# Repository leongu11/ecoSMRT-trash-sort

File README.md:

# ecoSMRT

## Overview
(this is my second README for this project -- I accidentally deleted the first one)
ecoSMRT is an edge AI project which determines if an article of trash is a recyclable (bottle) or not and sorts it accordingly.
It uses a refined version of MobileNetV2's CNN (convolutional neural networks) specifically for this task to make quality inferences. The model is around 60-70% accuracy when it comes to strong confidences over the 90% threshold.
I have logged nearly 45+ hours working on ecoSMRT as part of Hackclub's program, STASIS. Journal entries after every work session are also posted on the repository. 

## Incentive
Often times, managing waste can be overwhelming and done incorrectly. At the recycling level, nearly 76% of recyclables are lost at the household level (https://recyclingpartnership.org/residential-recycling-report/), and even those which are put into the recycling bin can be wrongly classified. As these wrongly-sorted articles of trash add up, the recycling process loses its efficiency, inflating unnecessary costs to over $3.5 billion yearly for the US (https://www.federalrecycling.com/industry-insights/common-recycling-mistakes-and-how-to-avoid-them/). As a direct result, recycling becomes more of a burden than a tool. Human error is exacerbating what recycling aims to fix: bettering the environment. Instead of looking towards refining the system, we should look to fix the root of the cause, our inaccuracies, by removing ourselves from the equation. AI is better than humans probably so like make a trash sorter ig 🤷‍♂️.

## Assembly Instructions
Use .stl files to print all 3d parts -- this includes the lid, the two edge mount pieces, the servo-lid adapter piece, and the camera mount (which is fixed to one of the edge mounts). NOTE: THE SERVO-LID ADAPTER PIECE REQUIRES A PAUSE IN THE PRINT TO SNAP ON THE HORN IN ORDER TO SEAL IT INSIDE THE PRINT! Slide the lid between the mounts to fix it in the center of the bin. Fasten the servo to the edge mount with two servo horn screws (which should have come with the servo) and connect the servo-lid adapter with the horn inside to the servo. Connect the adapter and the lid's extensions together-- glue is reccomended. The lid should now not rotate freely and rotating it should turn the servo, too. Attach a usb-c to usb-c onto the esp32 and camera and tape/glue to the top of the mount, allowing the camera to rest on the side of the mount. Connect the usb-c and flash the test-camera sketch onto the Xiao. It should return an IP to visit on the web to check the positioning of the camera. Adjust accordingly in order to have a clear view of the center of the bin. Using three jumper wires, solder the ends to both a capacitor and diode (optional, but recommended) using the schematic as a guide. Connect these jumpers to the servo, matching the power, ground, and signal accordingly. Once complete, flash the ecoSMRT-code onto the xiao. You should see inferences in the serial monitor and the lid rotating when those inferences pass the .95 -- or 95% -- threshold. Use the usb-c to power with any wall plug adapter or even laptop. 

## How ecoSMRT was made
I had originally settled for a more complex mechanical sorter, but the AI proved to be a challenge, so I simplified its design down to focus on firmware. The AI and curating a dataset which could yield decent results was also hard: At first, I was taking pre-existing datasets online, but the models were terrible. I did a lot of research and realized that I should probably use the native camera and setup for the training data, which turned out to work much better. Also, I switched from FOMO to MobileNet because like a month in I realized that image detection and classification were completely different (explanation found in journal). Everything else was relatively smooth sailing.

## Bill of Materials
| Component | Description | Cost | Link | 
|-----------|----------|-------------|-------|
| XIAO ESP32S3 Sense | Microcontroller with camera | $23.99 | [link](https://www.amazon.com/gp/product/B0CNL755KP/ref=ox_sc_act_title_2?smid=A2QTZX14X1D97I&th=1)
| MG90 servo | Sorting | $8.88 | [link](https://www.amazon.com/Seeed-Studio-XIAO-ESP32-Sense/dp/B0C69FFVHH?th=1)
## Hardware 
- MCU - Xiao ESP32S3-Sense w/ built-in camera module:
The Xiao ESP32 felt like the suitable choice because of its dual-core processors and built-in camera, which allowed the classification model to run smoothly locally, along with its GPIO capabilities.
Camera - OV2640 
- MG90 Microservo:
I have had my fair share of bad experience with the SG90 on multiple accounts, so I opted for its counterpart with metal-geared teeth, which seemed to be a good idea for tourque.

## Electronic Framework
I designed a schematic and PCB for this project in KiCAD

Schematic for wiring on perfboard:

PCB: 

I plan to use a perfboard using these as references for the physical project. 

## CAD / 3d Printed Parts

Parts are printed in PLA, amounting to around 300 grams of filament (although all my prototypes summed up to a kg spool)
These consist of the bin's lid, which revolves on small axis extensions. These pass through bores that connect to the edges of the lid, and, when connected to the servo, keep the lid at the set position. The mount for the ESP32 slides around the servo's housing and attach to its walls. Additionally, I have modeled small attachments to connect the two halves of the lid if it cannot be printed as one part. 

## Software & Dependencies
- Arduino IDE
- Edge Impulse CLI
- ESP32 Arduino Core 2.0.8+
- `bottleclassifications_inferencing` (included in `/lib`) (refined w/ Edge Impulse)
- servo/webserver libraries used for testing/deployment
  
here are some crappy inferences from my first few models:

### Image Classification VS Object Detection (written in a journal entry)
Classification observes the image as a whole and returns a confidence score; its only question to ask is: What is this thing in front of me? Detection has to decide three things: Are there multiple objects? What are the objects? Where are the objects? In this case, the model has to consider spatial data when moving forwards for its confidence, which takes a lot more computing power and is way too overkill for my project.

### How Image Classification Works
Image classification is tuning a pre-trained model for a specific need. My model, MobileNetV2 has already been trained on ImageNet with millions of classification data – its weights have already adjusted to finding curves, textures, and colors within an image. What the refining does is simply re-run these weights over the image (or vector with the image data) – there is a series of these filters (matricies which are averaged out to make smaller maps) that alter the feature map that compound on one another, so they take the last feature’s map, instead of the old image. In this way the filters are able to distinguish curves, then textures, then shapes, then the image itself – again stacking over itself. The result is a confidence score that can be achieved even with little data.

## Dataset
- Trained on [Edge Impulse](https://edgeimpulse.com)

## How It Works & Usage
Frames are fed into the CNN, which returns inferences for classifications in real time. If an inference exceeds the 90% confidence threshold, the servo adjusts lid in one direction or another, 'sorting' the article of trash. 

To use, place the trash on the lid in front of the camera and in any orientation and wait for the bin to sort before placing the second article of trash down. 

## Future Improvements
- Improving vision model by manually training on pytorch or by expanding dataset
- adding feet to the bin to stabilize and prevent shaking from disturbing classifications 💀
- adaptability

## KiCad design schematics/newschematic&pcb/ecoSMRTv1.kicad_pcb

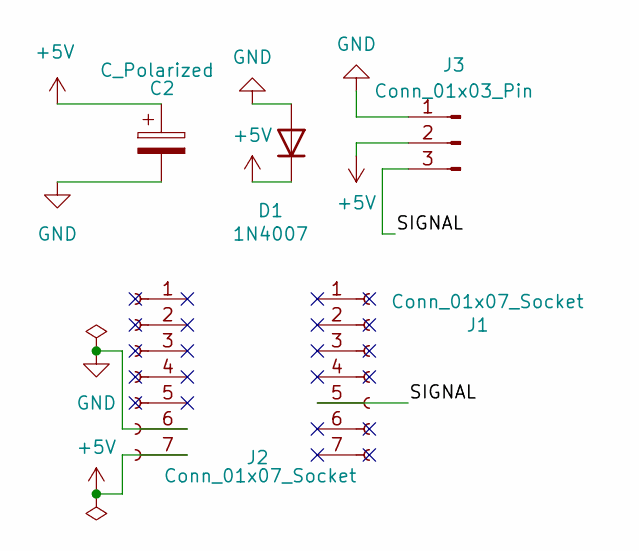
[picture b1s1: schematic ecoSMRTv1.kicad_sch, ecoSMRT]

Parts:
C2: C_Polarized; C_Radial_D5.0mm_H11.0mm_P2.00mm
D1: 1N4007; D_DO-41_SOD81_P10.16mm_Horizontal
J1, J2: Conn_01x07_Socket; PinSocket_1x07_P2.54mm_Vertical_SMD_Pin1Right
J3: Conn_01x03_Pin; PinHeader_1x03_P2.54mm_Vertical

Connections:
+5V: C2.1, D1.1 (K), J2.7, J3.2
/SIGNAL: J1.5 (Pin_5_5), J3.3
GND: C2.2, D1.2 (A), J2.6, J3.1

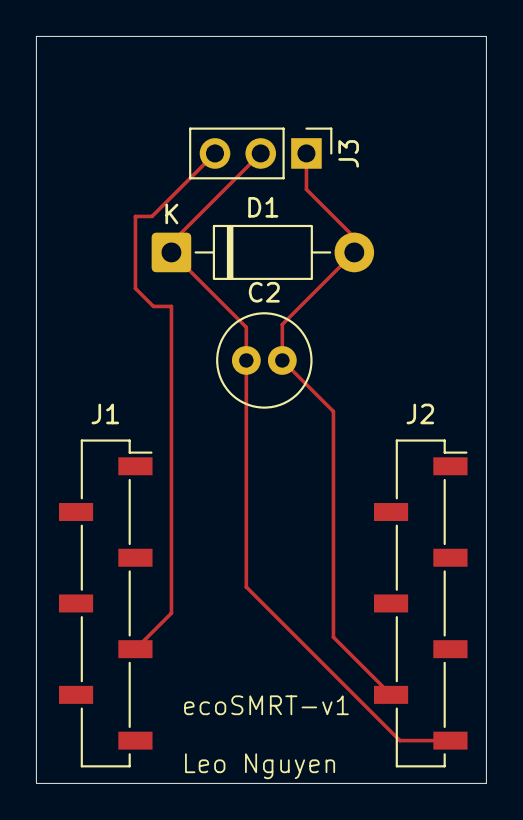
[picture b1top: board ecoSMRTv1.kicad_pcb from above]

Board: 2 copper layers, 25.0 x 41.5 mm, 5 parts (0 on the bottom side), 3 nets.

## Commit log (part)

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2026-05-03 project design over-- finished firmware finally
2026-05-03 gitignore and my CNN as a lib
2026-05-04 added cad files
2026-05-04 reorganized some files
2026-05-04 updated assembly w/electronic components included
2026-05-05 added new files with more metadatas
2026-05-05 made a second readme
    Added detailed project overview, hardware, software dependencies, dataset, and usage instructions.
2026-05-13 Enhance README with additional project details
    Added sections on electronic framework, CAD parts, and software dependencies. Updated incentive and how ecoSMRT was made sections for clarity.
2026-05-13 sources bruh
2026-05-14 new schematics and new PCB
2026-05-14 new pcb and schems
2026-06-07 gerber files
2026-06-28 new files redone and assembly instructions in readme
